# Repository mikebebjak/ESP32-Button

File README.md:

# ESP32-Button
ESP32 with a single button for one action and 0 current draw when not in use

I wanted to create a simple ESP32 PCB whose sole job was to send a single command over the Internet and then go completely dormant. Basically, the PCB, which is powered by 2x AA batteries, consumes 0 current when dormant (so not deep sleep) the button activates the power circuit to turn the ESP32 to run whatever code you want and then it shuts itself off.
The power design utilizes an boost circuit with an Enable pin that is pulled high by the button and then a GPIO on the ESP is used to keep it high until code execution is finished.

The use case I wanted it for was a simple Timesheet update for starting and finishing freelance work. The Google Sheets script is attached as well for those interested in this use case.

To use the Apps Script, simply create a Google Sheet with a sheet named Log and then add an App script and copy the contents of the txt file into it. Then give it permissions and deploy. You will need the URL to paste into the codes.h header so the ESP knows where to send it.

Note that this is not the most secure thing to be running with data of any sensitivity so please DYOR.

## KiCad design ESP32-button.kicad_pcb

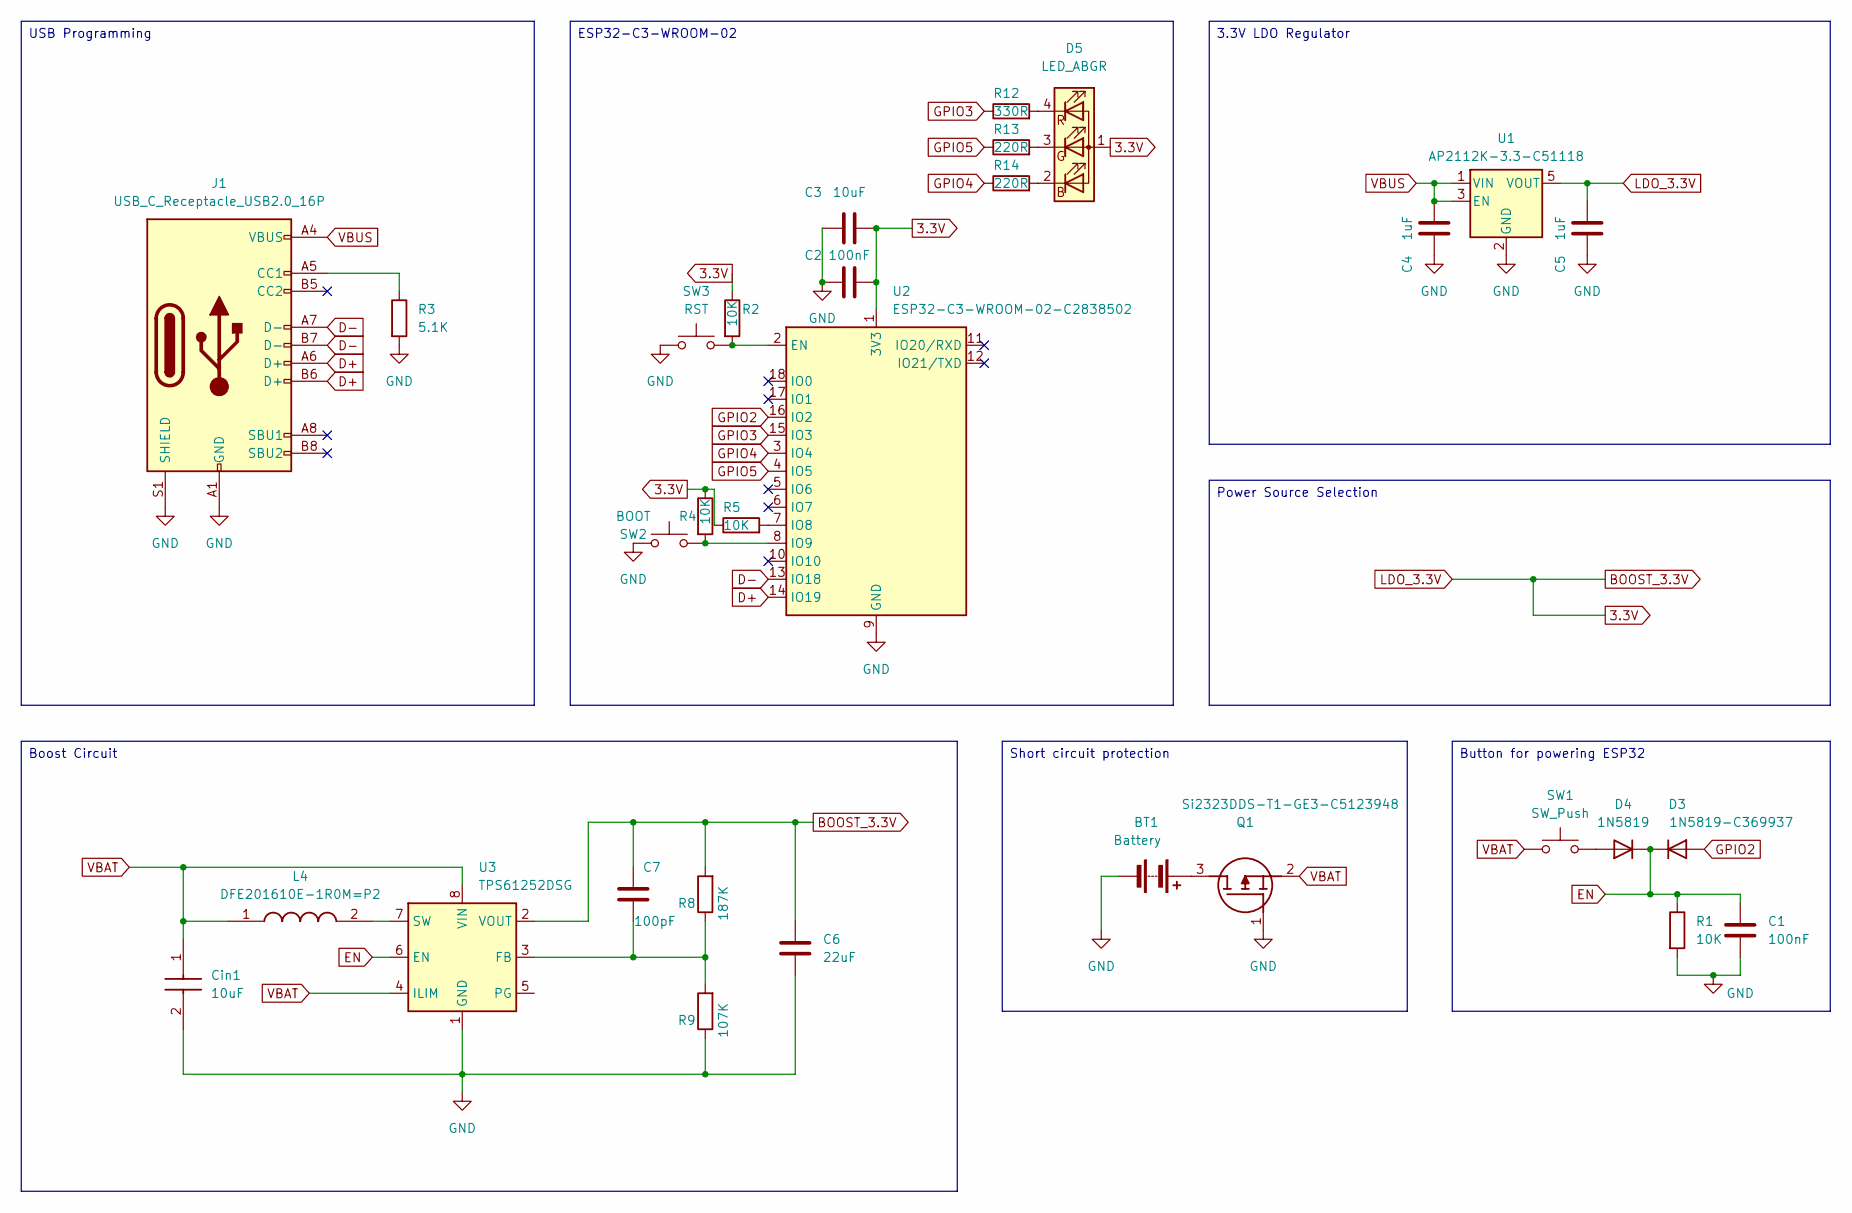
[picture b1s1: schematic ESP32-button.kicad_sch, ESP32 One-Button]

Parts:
BT1: Battery; BAT_BH2AAAPC
C1, C2: 100nF; C_0402_1005Metric
C3: 10uF; C_0805_2012Metric_Pad1.18x1.45mm_HandSolder
C4, C5: 1uF; C_0402_1005Metric
C6: 22uF; C_1210_3225Metric
C7: 100pF; C_0402_1005Metric
Cin1: 10uF; C_0805_2012Metric; Mouser Part Number 81-GRJ155R60J106ME1D
D3: 1N5819-C369937; D_SOD-323F
D4: 1N5819; D_SOD-323F
D5: LED_ABGR; TJ-S1615SW6TGLCCYRGB-A5
J1: USB_C_Receptacle_USB2.0_16P; USB_C_Receptacle_G-Switch_GT-USB-7010ASV
L4: DFE201610E-1R0M=P2; L_0805_2012Metric; Mouser Part Number 81-DFE201610E-1R0MP2
Q1: Si2323DDS-T1-GE3-C5123948; SOT-23-3; Mouser Part Number 78-SI2323DDS-T1-GE3
R1, R2, R4, R5: 10K; R_0402_1005Metric
R3: 5.1K; R_0603_1608Metric
R8: 187K; R_0402_1005Metric
R9: 107K; R_0402_1005Metric
R12: 330R; R_0402_1005Metric
R13, R14: 220R; R_0402_1005Metric
SW1: SW_Push; SW_TS04-66-50-BK-100-SMT
SW2: BOOT; SW_SPST_CK_KXT3
SW3: RST; SW_SPST_CK_KXT3
U1: AP2112K-3.3-C51118; SOT-23-5
U2: ESP32-C3-WROOM-02-C2838502; ESP32-C3-WROOM-02
U3: TPS61252DSG; WSON-8-1EP_2x2mm_P0.5mm_EP0.9x1.6mm

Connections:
3.3V: C2.2, C3.1, C5.2, C6.1, C7.1, D5.1 (A), R2.1, R4.1, R5.1, R8.2, U1.5 (VOUT), U2.1 (3V3), U3.2 (VOUT)
D+: J1.A6 (D+), J1.B6 (D+), U2.14 (IO19)
D-: J1.A7 (D-), J1.B7 (D-), U2.13 (IO18)
EN: C1.1, D3.1 (K), D4.1 (K), R1.1, U3.6 (EN)
GND: BT1.2 (-), C1.2, C2.1, C3.2, C4.1, C5.1, C6.2, Cin1.2, J1.A1 (GND), J1.A12 (GND), J1.B1 (GND), J1.B12 (GND), J1.S1 (SHIELD), Q1.1 (G), R1.2, R3.2, R9.1, SW2.1, SW3.1, U1.2 (GND), U2.9 (GND), U2.19 (GND), U3.1 (GND), U3.9 (GND)
GPIO2: D3.2 (A), U2.16 (IO2)
GPIO3: R12.1, U2.15 (IO3)
GPIO4: R14.1, U2.3 (IO4)
GPIO5: R13.1, U2.4 (IO5)
unnamed: BT1.1 (+), Q1.3 (D)
unnamed: D4.2 (A), SW1.2
unnamed: D5.2 (BK), R14.2
unnamed: D5.3 (GK), R13.2
unnamed: D5.4 (RK), R12.2
unnamed: J1.A5 (CC1), R3.1
unnamed: R2.2, SW3.2, U2.2 (EN)
unnamed: R5.2, U2.7 (IO8)
unnamed: R4.2, SW2.2, U2.8 (IO9)
unnamed: C7.2, R8.1, R9.2, U3.3 (FB)
unnamed: L4.2, U3.7 (SW)
VBAT: Cin1.1, L4.1, Q1.2 (S), SW1.1, U3.4 (ILIM), U3.8 (VIN)
VBUS: C4.2, J1.A4 (VBUS), J1.A9 (VBUS), J1.B4 (VBUS), J1.B9 (VBUS), U1.1 (VIN), U1.3 (EN)

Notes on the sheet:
3.3V LDO Regulator
Button for powering ESP32
USB Programming
Boost Circuit
Short circuit protection
Power Source Selection
ESP32-C3-WROOM-02

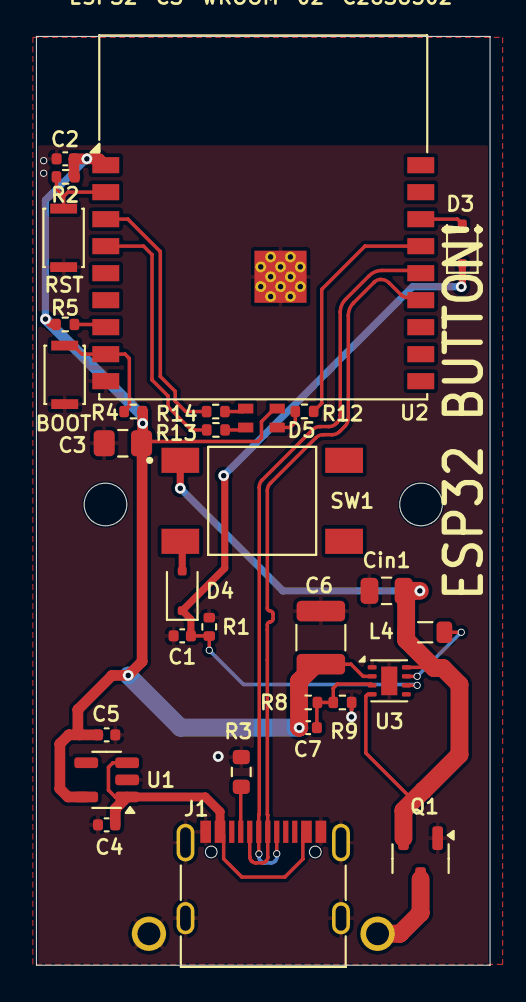
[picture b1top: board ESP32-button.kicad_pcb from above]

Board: 2 copper layers, 25.2 x 51.6 mm, 31 parts (1 on the bottom side), 22 nets.

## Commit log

2025-12-10 Update README.md
    added 3d render
2025-12-10 Add files via upload
    added Arduino files for the firmware
